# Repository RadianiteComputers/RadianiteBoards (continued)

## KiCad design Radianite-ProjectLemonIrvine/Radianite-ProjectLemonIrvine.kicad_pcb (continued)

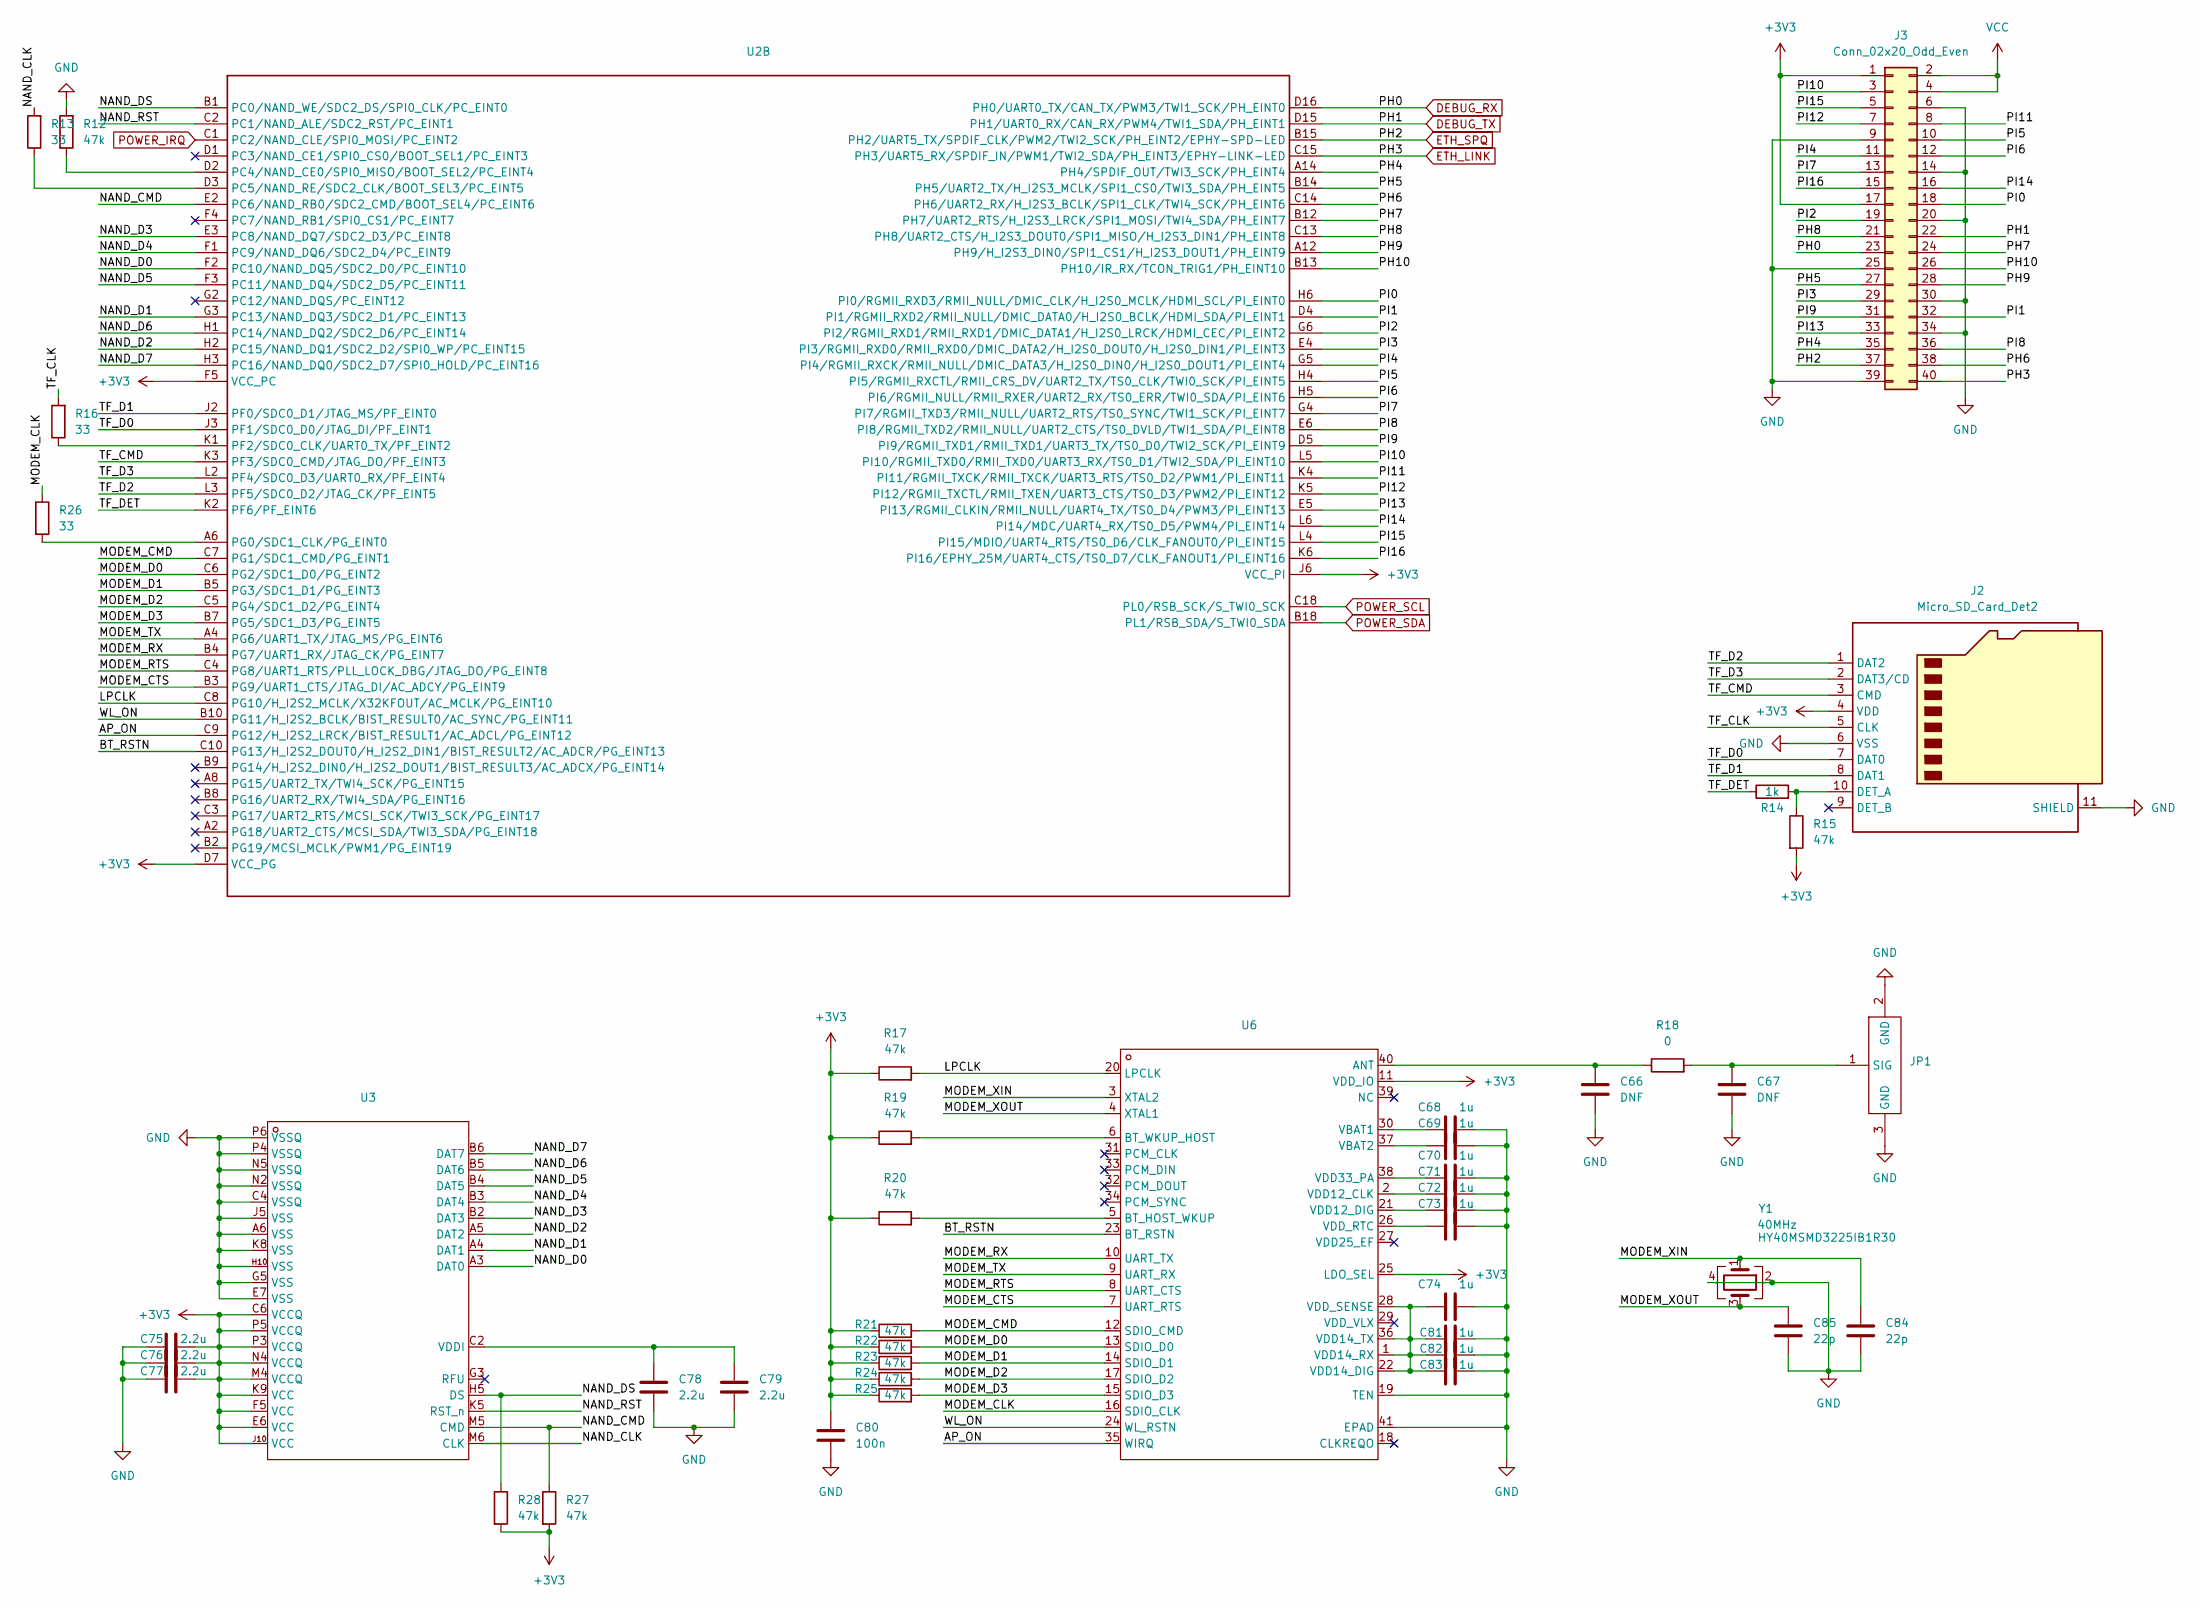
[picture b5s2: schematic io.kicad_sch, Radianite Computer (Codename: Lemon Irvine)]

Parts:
C66: DNF; C_0603_1608Metric
C67: DNF; C_0402_1005Metric
C68, C69, C70, C71, C72, C73, C74, C81, C82, C83: 1u; C_0402_1005Metric
C75, C76, C77, C78, C79: 2.2u; C_0402_1005Metric
C80: 100n; C_0402_1005Metric
C84, C85: 22p; C_0402_1005Metric
J2: Micro_SD_Card_Det2; microSD_HC_Molex_104031-0811
J3: Conn_02x20_Odd_Even; PinHeader_2x20_P2.54mm_Vertical
JP1: RF-SMD_734120114; Manufacturer Part U.FL-R-SMT-1(80); LCSC Part Name 3310472280，IPE-X板端 IPX接头，贴片
R12, R15, R17, R19, R20, R21, R22, R23, R24, R25, R27, R28: 47k; R_0402_1005Metric
R13, R16, R26: 33; R_0402_1005Metric
R14: 1k; R_0402_1005Metric
R18: 0; R_0402_1005Metric
U2: BGA284P65B1200_1400H125
U3: FBGA-153_L13.0-W11.5; Manufacturer Part EMMC04G-M627-A01
U6: QFN-40_L5.0-W5.0-P0.40-BL-EP3.4
Y1: 40MHz; Crystal_SMD_3225-4Pin_3.2x2.5mm

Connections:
+3V3: C75.2, C76.2, C77.2, C80.1, J2.4 (VDD), J3.1, J3.17, R15.2, R17.1, R19.1, R20.1, R21.1, R22.1, R23.1, R24.1, R25.1, R27.2, R28.2, U2.D7 (VCC_PG), U2.F5 (VCC_PC), U2.J6 (VCC_PI), U3.C6 (VCCQ), U3.E6 (VCC), U3.F5 (VCC), U3.J10 (VCC), U3.K9 (VCC), U3.M4 (VCCQ), U3.N4 (VCCQ), U3.P3 (VCCQ), U3.P5 (VCCQ), U6.11 (VDD_IO), U6.25 (LDO_SEL); also elsewhere on the board
/IO/AP_ON: U2.C9 (PG12/H_I2S2_LRCK/BIST_RESULT1/AC_ADCL/P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), U6.35 (WIRQ)
/IO/BT_RSTN: U2.C10 (PG13/H_I2S2_DOUT0/H_I2S2_DIN1/BIST_RESU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), U6.23 (BT_RSTN)
/IO/LPCLK: R17.2, U2.C8 (PG10/H_I2S2_MCLK/X32KFOUT/AC_MCLK/PG_EI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), U6.20 (LPCLK)
/IO/MODEM_CLK: R26.1, U6.16 (SDIO_CLK)
/IO/MODEM_CMD: R21.2, U2.C7 (PG1/SDC1_CMD/PG_EINT1), U6.12 (SDIO_CMD)
/IO/MODEM_CTS: U2.B3 (PG9/UART1_CTS/JTAG_DI/AC_ADCY/PG_EINT9), U6.7 (UART_RTS)
/IO/MODEM_D0: R22.2, U2.C6 (PG2/SDC1_D0/PG_EINT2), U6.13 (SDIO_D0)
/IO/MODEM_D1: R23.2, U2.B5 (PG3/SDC1_D1/PG_EINT3), U6.14 (SDIO_D1)
/IO/MODEM_D2: R24.2, U2.C5 (PG4/SDC1_D2/PG_EINT4), U6.17 (SDIO_D2)
/IO/MODEM_D3: R25.2, U2.B7 (PG5/SDC1_D3/PG_EINT5), U6.15 (SDIO_D3)
/IO/MODEM_RTS: U2.C4 (PG8/UART1_RTS/PLL_LOCK_DBG/JTAG_DO/PG_E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), U6.8 (UART_CTS)
/IO/MODEM_RX: U2.B4 (PG7/UART1_RX/JTAG_CK/PG_EINT7), U6.10 (UART_TX)
/IO/MODEM_TX: U2.A4 (PG6/UART1_TX/JTAG_MS/PG_EINT6), U6.9 (UART_RX)
/IO/MODEM_XIN: C84.1, U6.3 (XTAL2), Y1.1
/IO/MODEM_XOUT: C85.1, U6.4 (XTAL1), Y1.3
/IO/NAND_CLK: R13.2, U3.M6 (CLK)
/IO/NAND_CMD: R27.1, U2.E2 (PC6/NAND_RB0/SDC2_CMD/BOOT_SEL4/PC_EINT6), U3.M5 (CMD)
/IO/NAND_D0: U2.F2 (PC10/NAND_DQ5/SDC2_D0/PC_EINT10), U3.A3 (DAT0)
/IO/NAND_D1: U2.G3 (PC13/NAND_DQ3/SDC2_D1/PC_EINT13), U3.A4 (DAT1)
/IO/NAND_D2: U2.H2 (PC15/NAND_DQ1/SDC2_D2/SPI0_WP/PC_EINT15), U3.A5 (DAT2)
/IO/NAND_D3: U2.E3 (PC8/NAND_DQ7/SDC2_D3/PC_EINT8), U3.B2 (DAT3)
/IO/NAND_D4: U2.F1 (PC9/NAND_DQ6/SDC2_D4/PC_EINT9), U3.B3 (DAT4)
/IO/NAND_D5: U2.F3 (PC11/NAND_DQ4/SDC2_D5/PC_EINT11), U3.B4 (DAT5)
/IO/NAND_D6: U2.H1 (PC14/NAND_DQ2/SDC2_D6/PC_EINT14), U3.B5 (DAT6)
/IO/NAND_D7: U2.H3 (PC16/NAND_DQ0/SDC2_D7/SPI0_HOLD/PC_EINT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), U3.B6 (DAT7)
/IO/NAND_DS: R28.1, U2.B1 (PC0/NAND_WE/SDC2_DS/SPI0_CLK/PC_EINT0), U3.H5 (DS)
/IO/NAND_RST: U2.C2 (PC1/NAND_ALE/SDC2_RST/PC_EINT1), U3.K5 (RST_n)
/IO/PH4: J3.35, U2.A14 (PH4/SPDIF_OUT/TWI3_SCK/PH_EINT4)
/IO/PH5: J3.27, U2.B14 (PH5/UART2_TX/H_I2S3_MCLK/SPI1_CS0/TWI3_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)
/IO/PH6: J3.38, U2.C14 (PH6/UART2_RX/H_I2S3_BCLK/SPI1_CLK/TWI4_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)
/IO/PH7: J3.24, U2.B12 (PH7/UART2_RTS/H_I2S3_LRCK/SPI1_MOSI/TWI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)
/IO/PH8: J3.21, U2.C13 (PH8/UART2_CTS/H_I2S3_DOUT0/SPI1_MISO/H_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)
/IO/PH9: J3.28, U2.A12 (PH9/H_I2S3_DIN0/SPI1_CS1/H_I2S3_DOUT1/P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)
/IO/PH10: J3.26, U2.B13 (PH10/IR_RX/TCON_TRIG1/PH_EINT10)
/IO/PI0: J3.18, U2.H6 (PI0/RGMII_RXD3/RMII_NULL/DMIC_CLK/H_I2S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)
/IO/PI1: J3.32, U2.D4 (PI1/RGMII_RXD2/RMII_NULL/DMIC_DATA0/H_I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)
/IO/PI2: J3.19, U2.G6 (PI2/RGMII_RXD1/RMII_RXD1/DMIC_DATA1/H_I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)
/IO/PI3: J3.29, U2.E4 (PI3/RGMII_RXD0/RMII_RXD0/DMIC_DATA2/H_I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)
/IO/PI4: J3.11, U2.G5 (PI4/RGMII_RXCK/RMII_NULL/DMIC_DATA3/H_I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)
/IO/PI5: J3.10, U2.H4 (PI5/RGMII_RXCTL/RMII_CRS_DV/UART2_TX/TS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)
/IO/PI6: J3.12, U2.H5 (PI6/RGMII_NULL/RMII_RXER/UART2_RX/TS0_E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)
/IO/PI7: J3.13, U2.G4 (PI7/RGMII_TXD3/RMII_NULL/UART2_RTS/TS0_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)
/IO/PI8: J3.36, U2.E6 (PI8/RGMII_TXD2/RMII_NULL/UART2_CTS/TS0_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)
/IO/PI9: J3.31, U2.D5 (PI9/RGMII_TXD1/RMII_TXD1/UART3_TX/TS0_D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)
/IO/PI10: J3.3, U2.L5 (PI10/RGMII_TXD0/RMII_TXD0/UART3_RX/TS0_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)
/IO/PI11: J3.8, U2.K4 (PI11/RGMII_TXCK/RMII_TXCK/UART3_RTS/TS0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)
/IO/PI12: J3.7, U2.K5 (PI12/RGMII_TXCTL/RMII_TXEN/UART3_CTS/TS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)
/IO/PI13: J3.33, U2.E5 (PI13/RGMII_CLKIN/RMII_NULL/UART4_TX/TS0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)
/IO/PI14: J3.16, U2.L6 (PI14/MDC/UART4_RX/TS0_D5/PWM4/PI_EINT14)
/IO/PI15: J3.5, U2.L4 (PI15/MDIO/UART4_RTS/TS0_D6/CLK_FANOUT0/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)
/IO/PI16: J3.15, U2.K6 (PI16/EPHY_25M/UART4_CTS/TS0_D7/CLK_FANO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)
/IO/TF_CLK: J2.5 (CLK), R16.2
/IO/TF_CMD: J2.3 (CMD), U2.K3 (PF3/SDC0_CMD/JTAG_DO/PF_EINT3)
/IO/TF_D0: J2.7 (DAT0), U2.J3 (PF1/SDC0_D0/JTAG_DI/PF_EINT1)
/IO/TF_D1: J2.8 (DAT1), U2.J2 (PF0/SDC0_D1/JTAG_MS/PF_EINT0)
/IO/TF_D2: J2.1 (DAT2), U2.L3 (PF5/SDC0_D2/JTAG_CK/PF_EINT5)
/IO/TF_D3: J2.2 (DAT3/CD), U2.L2 (PF4/SDC0_D3/UART0_RX/PF_EINT4)
/IO/TF_DET: R14.1, U2.K2 (PF6/PF_EINT6)
/IO/WL_ON: U2.B10 (PG11/H_I2S2_BCLK/BIST_RESULT0/AC_SYNC/P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), U6.24 (WL_RSTN)
DEBUG_RX: J3.23, U2.D16 (PH0/UART0_TX/CAN_TX/PWM3/TWI1_SCK/PH_EI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); also elsewhere on the board
DEBUG_TX: J3.22, U2.D15 (PH1/UART0_RX/CAN_RX/PWM4/TWI1_SDA/PH_EI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); also elsewhere on the board
ETH_LINK: J3.40, U2.C15 (PH3/UART5_RX/SPDIF_IN/PWM1/TWI2_SDA/PH_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); also elsewhere on the board
ETH_SPQ: J3.37, U2.B15 (PH2/UART5_TX/SPDIF_CLK/PWM2/TWI2_SCK/PH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); also elsewhere on the board
GND: C66.2, C67.2, C68.2, C69.2, C70.2, C71.2, C72.2, C73.2, C74.2, C75.1, C76.1, C77.1, C78.2, C79.2, C80.2, C81.2, C82.2, C83.2, C84.2, C85.2, J2.6 (VSS), J2.11 (SHIELD), J3.6, J3.9, J3.14, J3.20, J3.25, J3.30, J3.34, J3.39, JP1.2 (GND), JP1.3 (GND), R12.2, U3.A6 (VSS), U3.C4 (VSSQ), U3.E7 (VSS), U3.G5 (VSS), U3.H10 (VSS), U3.J5 (VSS), U3.K8 (VSS), U3.N2 (VSSQ), U3.N5 (VSSQ), U3.P4 (VSSQ), U3.P6 (VSSQ), U6.19 (TEN), U6.41 (EPAD), Y1.2, Y1.4; also elsewhere on the board
unnamed: J2.10 (DET_A), R14.2, R15.1
unnamed: C67.1, JP1.1 (SIG), R18.2
unnamed: R12.1, U2.D2 (PC4/NAND_CE0/SPI0_MISO/BOOT_SEL2/PC_EIN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)
unnamed: R13.1, U2.D3 (PC5/NAND_RE/SDC2_CLK/BOOT_SEL3/PC_EINT5)
unnamed: R16.1, U2.K1 (PF2/SDC0_CLK/UART0_TX/PF_EINT2)
unnamed: R26.2, U2.A6 (PG0/SDC1_CLK/PG_EINT0)
unnamed: C78.1, C79.1, U3.C2 (VDDI)
unnamed: C66.1, R18.1, U6.40 (ANT)
unnamed: R20.2, U6.5 (BT_HOST_WKUP)
unnamed: R19.2, U6.6 (BT_WKUP_HOST)
unnamed: C68.1, U6.30 (VBAT1)
unnamed: C69.1, U6.37 (VBAT2)
unnamed: C71.1, U6.2 (VDD12_CLK)
unnamed: C72.1, U6.21 (VDD12_DIG)
unnamed: C74.1, C81.1, C82.1, C83.1, U6.1 (VDD14_RX), U6.22 (VDD14_DIG), U6.28 (VDD_SENSE), U6.36 (VDD14_TX)
unnamed: C70.1, U6.38 (VDD33_PA)
unnamed: C73.1, U6.26 (VDD_RTC)
POWER_IRQ: U2.C1 (PC2/NAND_CLE/SPI0_MOSI/PC_EINT2); also elsewhere on the board
POWER_SCL: U2.C18 (PL0/RSB_SCK/S_TWI0_SCK); also elsewhere on the board
POWER_SDA: U2.B18 (PL1/RSB_SDA/S_TWI0_SDA); also elsewhere on the board
VBUS: J3.2, J3.4; also elsewhere on the board

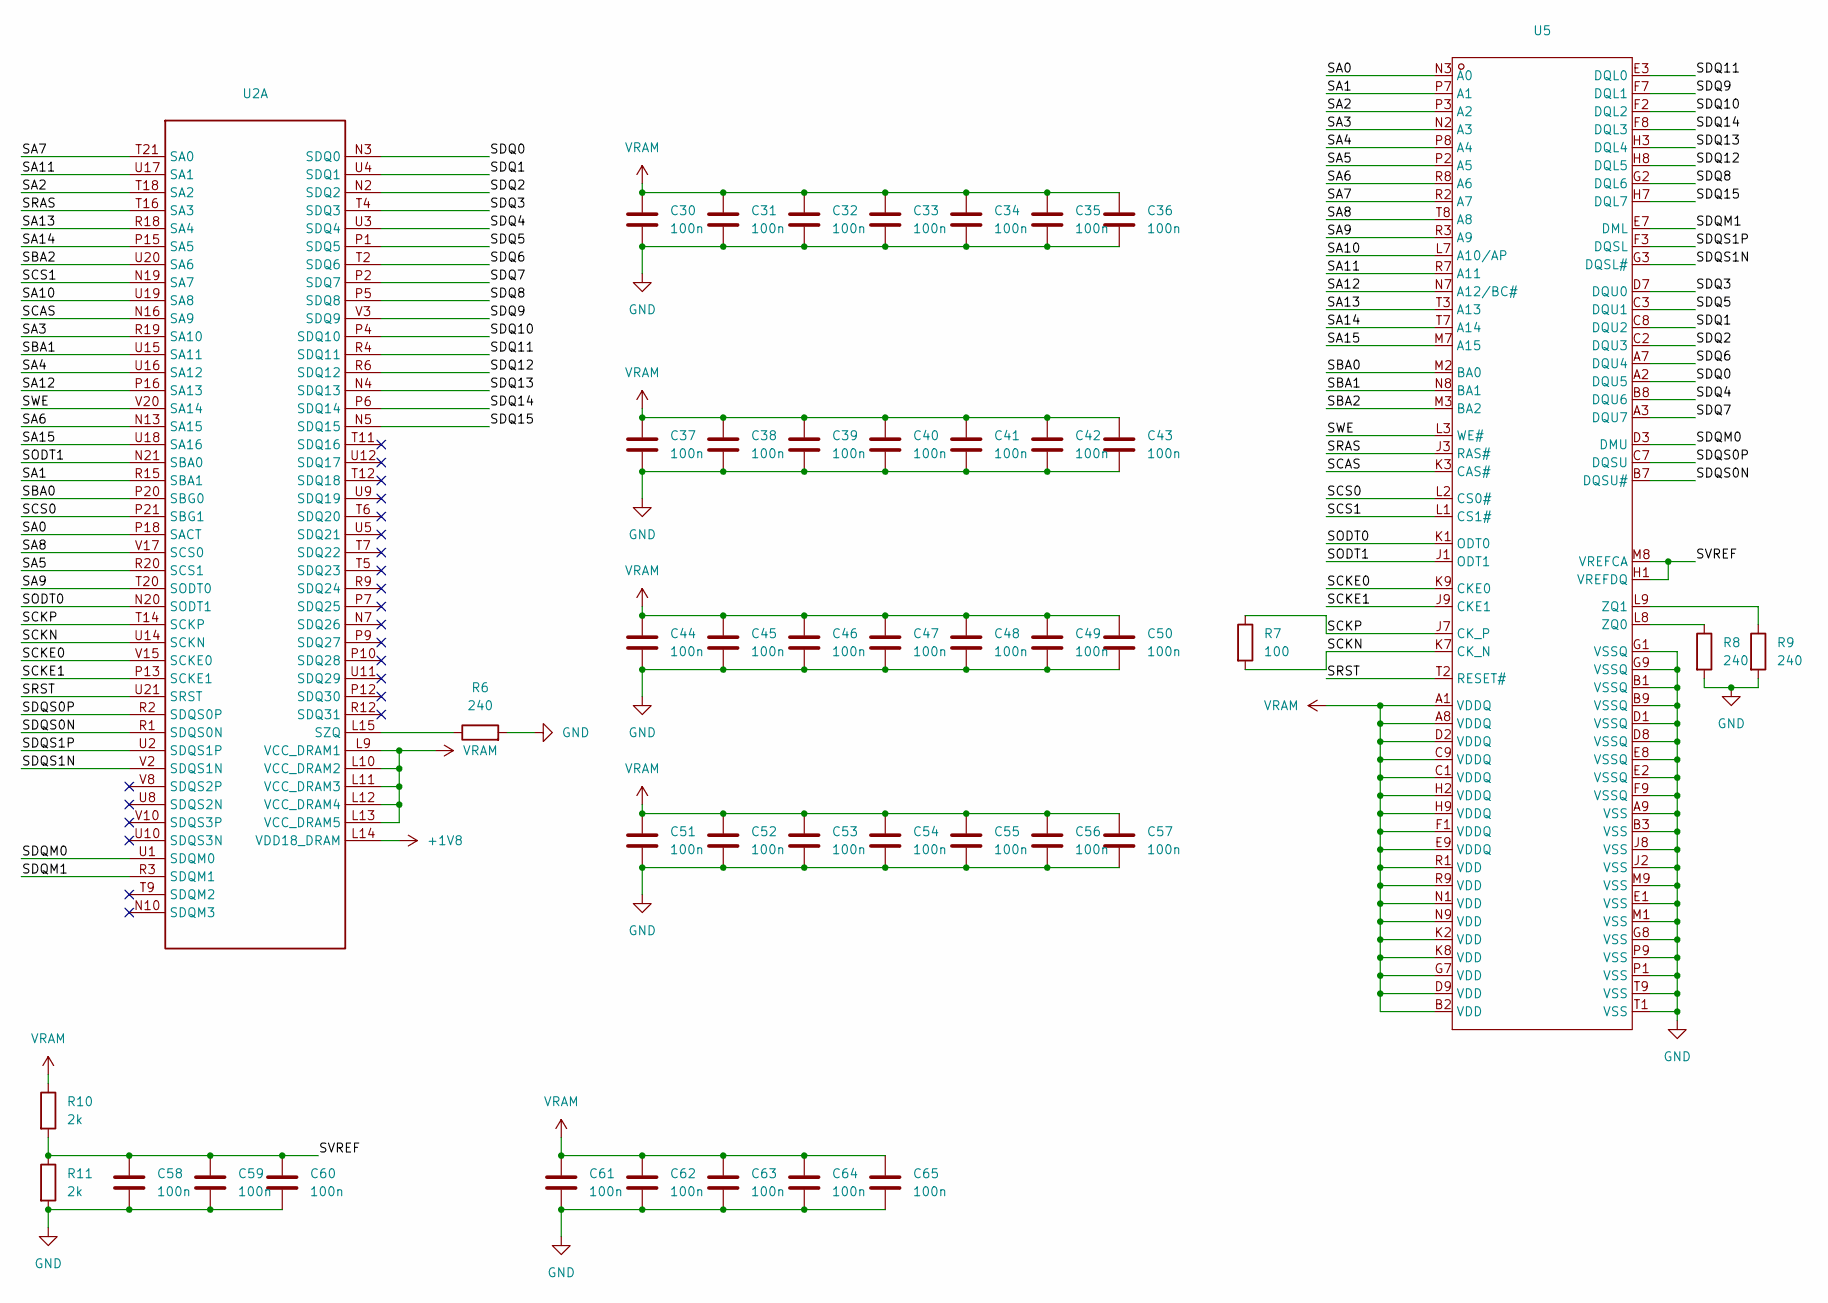
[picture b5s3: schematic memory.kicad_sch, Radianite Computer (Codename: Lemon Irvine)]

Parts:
C30, C31, C32, C33, C34, C35, C36, C37, C38, C39, C40, C41, C42, C43, C44, C45, C46, C47, C48, C49, C50, C51, C52, C53, C54, C55, C56, C57, C58, C59, C60, C61, C62, C63, C64, C65: 100n; C_0402_1005Metric
R6, R8, R9: 240; R_0402_1005Metric
R7: 100; R_0402_1005Metric
R10, R11: 2k; R_0402_1005Metric
U2: BGA284P65B1200_1400H125
U5: FBGA96; Manufacturer Part H5TQ4G63EFR-RDC

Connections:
+1V8: U2.L14 (VDD18_DRAM); also elsewhere on the board
/Memory/SA0: U2.P18 (SACT), U5.N3 (A0)
/Memory/SA1: U2.R15 (SBA1), U5.P7 (A1)
/Memory/SA2: U2.T18 (SA2), U5.P3 (A2)
/Memory/SA3: U2.R19 (SA10), U5.N2 (A3)
/Memory/SA4: U2.U16 (SA12), U5.P8 (A4)
/Memory/SA5: U2.R20 (SCS1), U5.P2 (A5)
/Memory/SA6: U2.N13 (SA15), U5.R8 (A6)
/Memory/SA7: U2.T21 (SA0), U5.R2 (A7)
/Memory/SA8: U2.V17 (SCS0), U5.T8 (A8)
/Memory/SA9: U2.T20 (SODT0), U5.R3 (A9)
/Memory/SA10: U2.U19 (SA8), U5.L7 (A10/AP)
/Memory/SA11: U2.U17 (SA1), U5.R7 (A11)
/Memory/SA12: U2.P16 (SA13), U5.N7 (A12/BC#)
/Memory/SA13: U2.R18 (SA4), U5.T3 (A13)
/Memory/SA14: U2.P15 (SA5), U5.T7 (A14)
/Memory/SA15: U2.U18 (SA16), U5.M7 (A15)
/Memory/SBA0: U2.P20 (SBG0), U5.M2 (BA0)
/Memory/SBA1: U2.U15 (SA11), U5.N8 (BA1)
/Memory/SBA2: U2.U20 (SA6), U5.M3 (BA2)
/Memory/SCAS: U2.N16 (SA9), U5.K3 (CAS#)
/Memory/SCKE0: U2.V15 (SCKE0), U5.K9 (CKE0)
/Memory/SCKE1: U2.P13 (SCKE1), U5.J9 (CKE1)
/Memory/SCKN: R7.2, U2.U14 (SCKN), U5.K7 (CK_N)
/Memory/SCKP: R7.1, U2.T14 (SCKP), U5.J7 (CK_P)
/Memory/SCS0: U2.P21 (SBG1), U5.L2 (CS0#)
/Memory/SCS1: U2.N19 (SA7), U5.L1 (CS1#)
/Memory/SDQ0: U2.N3 (SDQ0), U5.A2 (DQU5)
/Memory/SDQ1: U2.U4 (SDQ1), U5.C8 (DQU2)
/Memory/SDQ2: U2.N2 (SDQ2), U5.C2 (DQU3)
/Memory/SDQ3: U2.T4 (SDQ3), U5.D7 (DQU0)
/Memory/SDQ4: U2.U3 (SDQ4), U5.B8 (DQU6)
/Memory/SDQ5: U2.P1 (SDQ5), U5.C3 (DQU1)
/Memory/SDQ6: U2.T2 (SDQ6), U5.A7 (DQU4)
/Memory/SDQ7: U2.P2 (SDQ7), U5.A3 (DQU7)
/Memory/SDQ8: U2.P5 (SDQ8), U5.G2 (DQL6)
/Memory/SDQ9: U2.V3 (SDQ9), U5.F7 (DQL1)
/Memory/SDQ10: U2.P4 (SDQ10), U5.F2 (DQL2)
/Memory/SDQ11: U2.R4 (SDQ11), U5.E3 (DQL0)
/Memory/SDQ12: U2.R6 (SDQ12), U5.H8 (DQL5)
/Memory/SDQ13: U2.N4 (SDQ13), U5.H3 (DQL4)
/Memory/SDQ14: U2.P6 (SDQ14), U5.F8 (DQL3)
/Memory/SDQ15: U2.N5 (SDQ15), U5.H7 (DQL7)
/Memory/SDQM0: U2.U1 (SDQM0), U5.D3 (DMU)
/Memory/SDQM1: U2.R3 (SDQM1), U5.E7 (DML)
/Memory/SDQS0N: U2.R1 (SDQS0N), U5.B7 (DQSU#)
/Memory/SDQS0P: U2.R2 (SDQS0P), U5.C7 (DQSU)
/Memory/SDQS1N: U2.V2 (SDQS1N), U5.G3 (DQSL#)
/Memory/SDQS1P: U2.U2 (SDQS1P), U5.F3 (DQSL)
/Memory/SODT0: U2.N20 (SODT1), U5.K1 (ODT0)
/Memory/SODT1: U2.N21 (SBA0), U5.J1 (ODT1)
/Memory/SRAS: U2.T16 (SA3), U5.J3 (RAS#)
/Memory/SRST: U2.U21 (SRST), U5.T2 (RESET#)
/Memory/SVREF: C58.1, C59.1, C60.1, R10.2, R11.1, U5.H1 (VREFDQ), U5.M8 (VREFCA)
/Memory/SWE: U2.V20 (SA14), U5.L3 (WE#)
GND: C30.2, C31.2, C32.2, C33.2, C34.2, C35.2, C36.2, C37.2, C38.2, C39.2, C40.2, C41.2, C42.2, C43.2, C44.2, C45.2, C46.2, C47.2, C48.2, C49.2, C50.2, C51.2, C52.2, C53.2, C54.2, C55.2, C56.2, C57.2, C58.2, C59.2, C60.2, C61.2, C62.2, C63.2, C64.2, C65.2, R6.2, R8.2, R9.2, R11.2, U5.A9 (VSS), U5.B1 (VSSQ), U5.B3 (VSS), U5.B9 (VSSQ), U5.D1 (VSSQ), U5.D8 (VSSQ), U5.E1 (VSS), U5.E2 (VSSQ), U5.E8 (VSSQ), U5.F9 (VSSQ), U5.G1 (VSSQ), U5.G8 (VSS), U5.G9 (VSSQ), U5.J2 (VSS), U5.J8 (VSS), U5.M1 (VSS), U5.M9 (VSS), U5.P1 (VSS), U5.P9 (VSS), U5.T1 (VSS), U5.T9 (VSS); also elsewhere on the board
unnamed: R6.1, U2.L15 (SZQ)
unnamed: R8.1, U5.L8 (ZQ0)
unnamed: R9.1, U5.L9 (ZQ1)
VRAM: C30.1, C31.1, C32.1, C33.1, C34.1, C35.1, C36.1, C37.1, C38.1, C39.1, C40.1, C41.1, C42.1, C43.1, C44.1, C45.1, C46.1, C47.1, C48.1, C49.1, C50.1, C51.1, C52.1, C53.1, C54.1, C55.1, C56.1, C57.1, C61.1, C62.1, C63.1, C64.1, C65.1, R10.1, U2.L9 (VCC_DRAM1), U2.L10 (VCC_DRAM2), U2.L11 (VCC_DRAM3), U2.L12 (VCC_DRAM4), U2.L13 (VCC_DRAM5), U5.A1 (VDDQ), U5.A8 (VDDQ), U5.B2 (VDD), U5.C1 (VDDQ), U5.C9 (VDDQ), U5.D2 (VDDQ), U5.D9 (VDD), U5.E9 (VDDQ), U5.F1 (VDDQ), U5.G7 (VDD), U5.H2 (VDDQ), U5.H9 (VDDQ), U5.K2 (VDD), U5.K8 (VDD), U5.N1 (VDD), U5.N9 (VDD), U5.R1 (VDD), U5.R9 (VDD); also elsewhere on the board

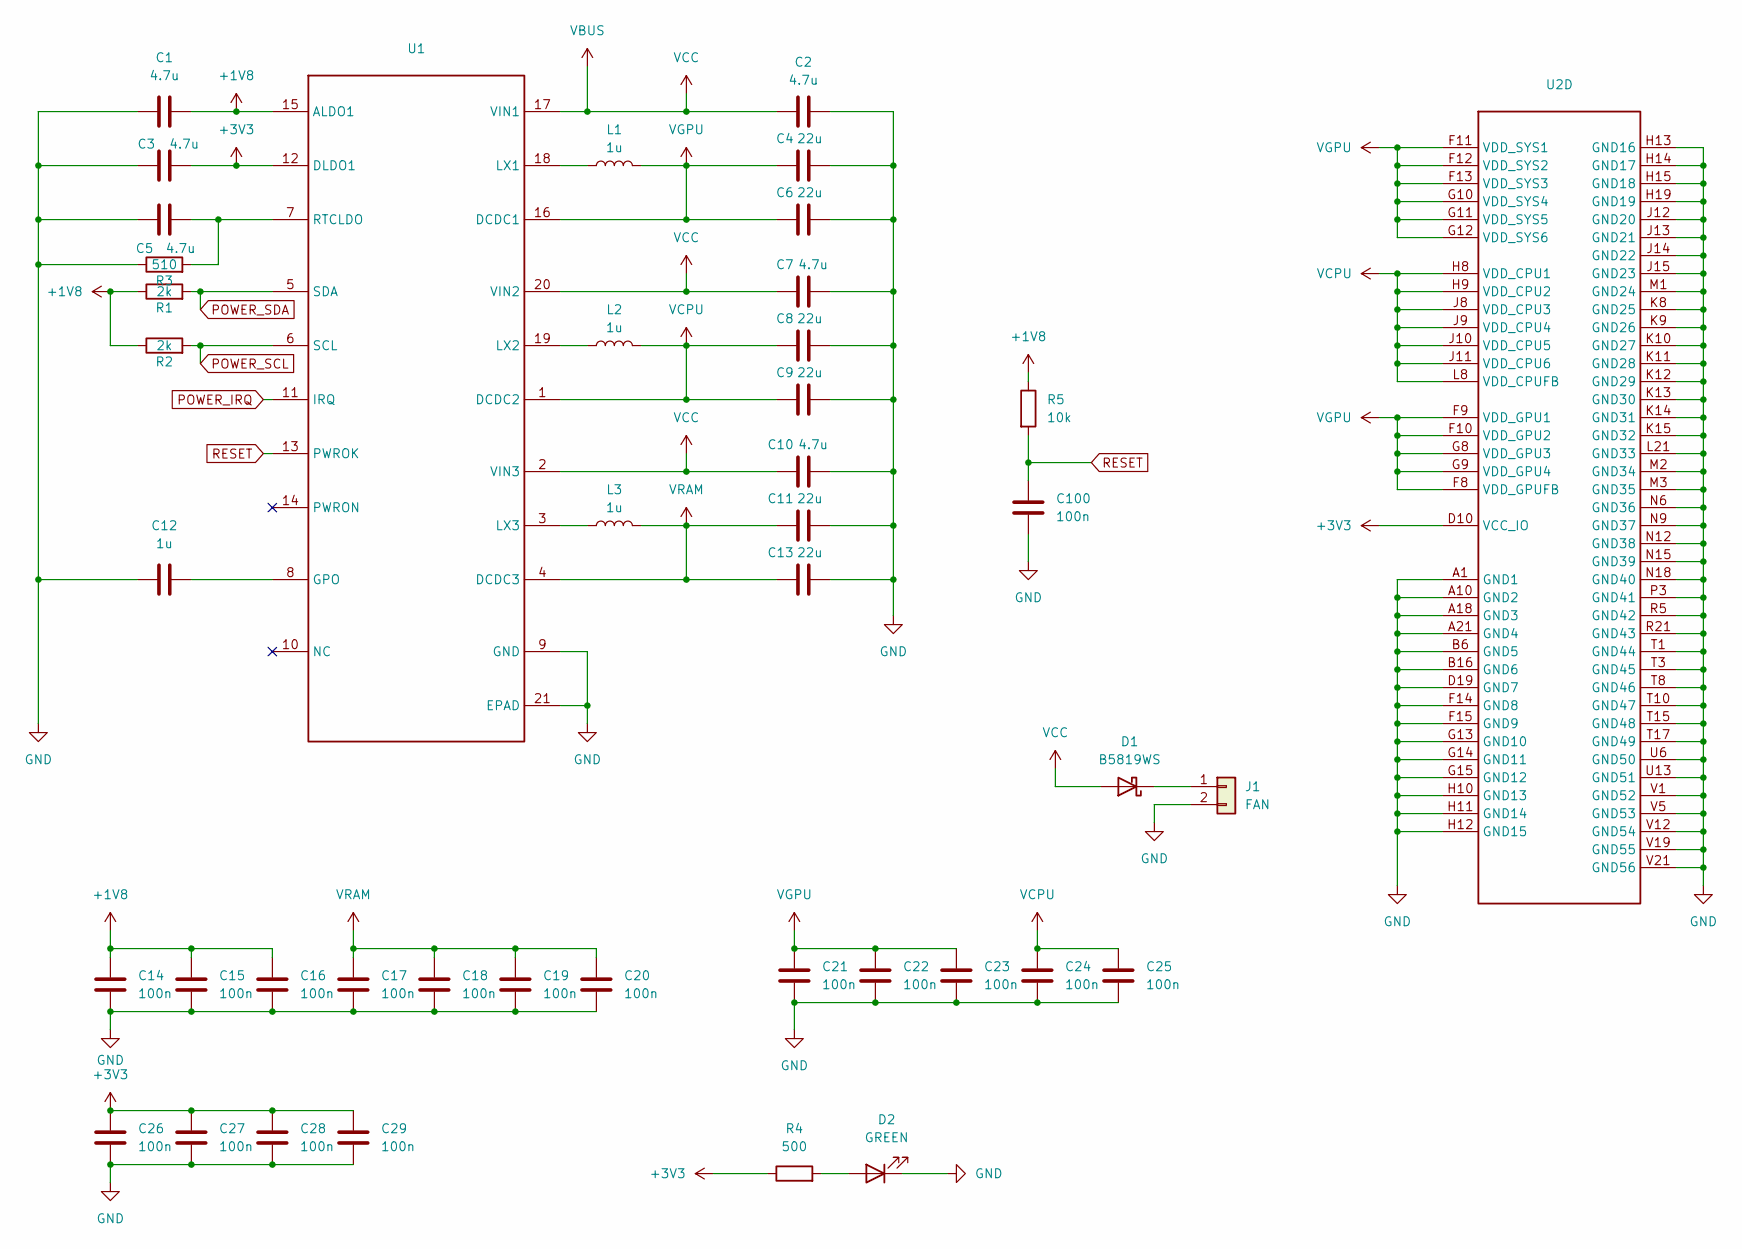
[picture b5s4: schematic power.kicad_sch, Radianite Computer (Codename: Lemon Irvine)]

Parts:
C1, C2, C3, C5, C7, C10: 4.7u; C_0402_1005Metric
C4, C6, C8, C9, C11, C13: 22u; C_0402_1005Metric
C12: 1u; C_0402_1005Metric
C14, C15, C16, C17, C18, C19, C20, C21, C22, C23, C24, C25, C26, C27, C28, C29, C100: 100n; C_0402_1005Metric
D1: B5819WS; D_SOD-323
D2: GREEN; LED_0402_1005Metric
J1: FAN; JST_PH_B2B-PH-K_1x02_P2.00mm_Vertical
L1, L2, L3: 1u; L_1008_2520Metric
R1, R2: 2k; R_0402_1005Metric
R3: 510; R_0402_1005Metric
R4: 500; R_0402_1005Metric
R5: 10k; R_0402_1005Metric
U1: WQFN-20_L3.0-W3.0-P0.40-BL-EP
U2: BGA284P65B1200_1400H125

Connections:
+1V8: C1.2, C14.1, C15.1, C16.1, R1.1, R2.1, R5.1, U1.15 (ALDO1); also elsewhere on the board
+3V3: C3.2, C26.1, C27.1, C28.1, C29.1, R4.1, U1.12 (DLDO1), U2.D10 (VCC_IO); also elsewhere on the board
GND: C1.1, C2.2, C3.1, C4.2, C5.1, C6.2, C7.2, C8.2, C9.2, C10.2, C11.2, C12.1, C13.2, C14.2, C15.2, C16.2, C17.2, C18.2, C19.2, C20.2, C21.2, C22.2, C23.2, C24.2, C25.2, C26.2, C27.2, C28.2, C29.2, C100.2, D2.1 (K), J1.2, R3.1, U1.9 (GND), U1.21 (EPAD), U2.A1 (GND1), U2.A10 (GND2), U2.A18 (GND3), U2.A21 (GND4), U2.B6 (GND5), U2.B16 (GND6), U2.D19 (GND7), U2.F14 (GND8), U2.F15 (GND9), U2.G13 (GND10), U2.G14 (GND11), U2.G15 (GND12), U2.H10 (GND13), U2.H11 (GND14), U2.H12 (GND15), U2.H13 (GND16), U2.H14 (GND17), U2.H15 (GND18), U2.H19 (GND19), U2.J12 (GND20), U2.J13 (GND21), U2.J14 (GND22), U2.J15 (GND23), U2.K8 (GND25), U2.K9 (GND26), U2.K10 (GND27), U2.K11 (GND28), U2.K12 (GND29), U2.K13 (GND30), U2.K14 (GND31), U2.K15 (GND32), U2.L21 (GND33), U2.M1 (GND24), U2.M2 (GND34), U2.M3 (GND35), U2.N6 (GND36), U2.N9 (GND37), U2.N12 (GND38), U2.N15 (GND39), U2.N18 (GND40), U2.P3 (GND41), U2.R5 (GND42), U2.R21 (GND43), U2.T1 (GND44), U2.T3 (GND45), U2.T8 (GND46), U2.T10 (GND47), U2.T15 (GND48), U2.T17 (GND49), U2.U6 (GND50), U2.U13 (GND51), U2.V1 (GND52), U2.V5 (GND53), U2.V12 (GND54), U2.V19 (GND55), U2.V21 (GND56); also elsewhere on the board
unnamed: D1.1 (K), J1.1
unnamed: D2.2 (A), R4.2
unnamed: C12.2, U1.8 (GPO)
unnamed: L1.1, U1.18 (LX1)
unnamed: L2.1, U1.19 (LX2)
unnamed: L3.1, U1.3 (LX3)
unnamed: C5.2, R3.2, U1.7 (RTCLDO)
POWER_IRQ: U1.11 (IRQ); also elsewhere on the board
POWER_SCL: R2.2, U1.6 (SCL); also elsewhere on the board
POWER_SDA: R1.2, U1.5 (SDA); also elsewhere on the board
RESET: C100.1, R5.2, U1.13 (PWROK); also elsewhere on the board
VBUS: C2.1, C7.1, C10.1, D1.2 (A), U1.2 (VIN3), U1.17 (VIN1), U1.20 (VIN2); also elsewhere on the board
VCPU: C8.1, C9.1, C24.1, C25.1, L2.2, U1.1 (DCDC2), U2.H8 (VDD_CPU1), U2.H9 (VDD_CPU2), U2.J8 (VDD_CPU3), U2.J9 (VDD_CPU4), U2.J10 (VDD_CPU5), U2.J11 (VDD_CPU6), U2.L8 (VDD_CPUFB)
VGPU: C4.1, C6.1, C21.1, C22.1, C23.1, L1.2, U1.16 (DCDC1), U2.F8 (VDD_GPUFB), U2.F9 (VDD_GPU1), U2.F10 (VDD_GPU2), U2.F11 (VDD_SYS1), U2.F12 (VDD_SYS2), U2.F13 (VDD_SYS3), U2.G8 (VDD_GPU3), U2.G9 (VDD_GPU4), U2.G10 (VDD_SYS4), U2.G11 (VDD_SYS5), U2.G12 (VDD_SYS6)
VRAM: C11.1, C13.1, C17.1, C18.1, C19.1, C20.1, L3.2, U1.4 (DCDC3); also elsewhere on the board

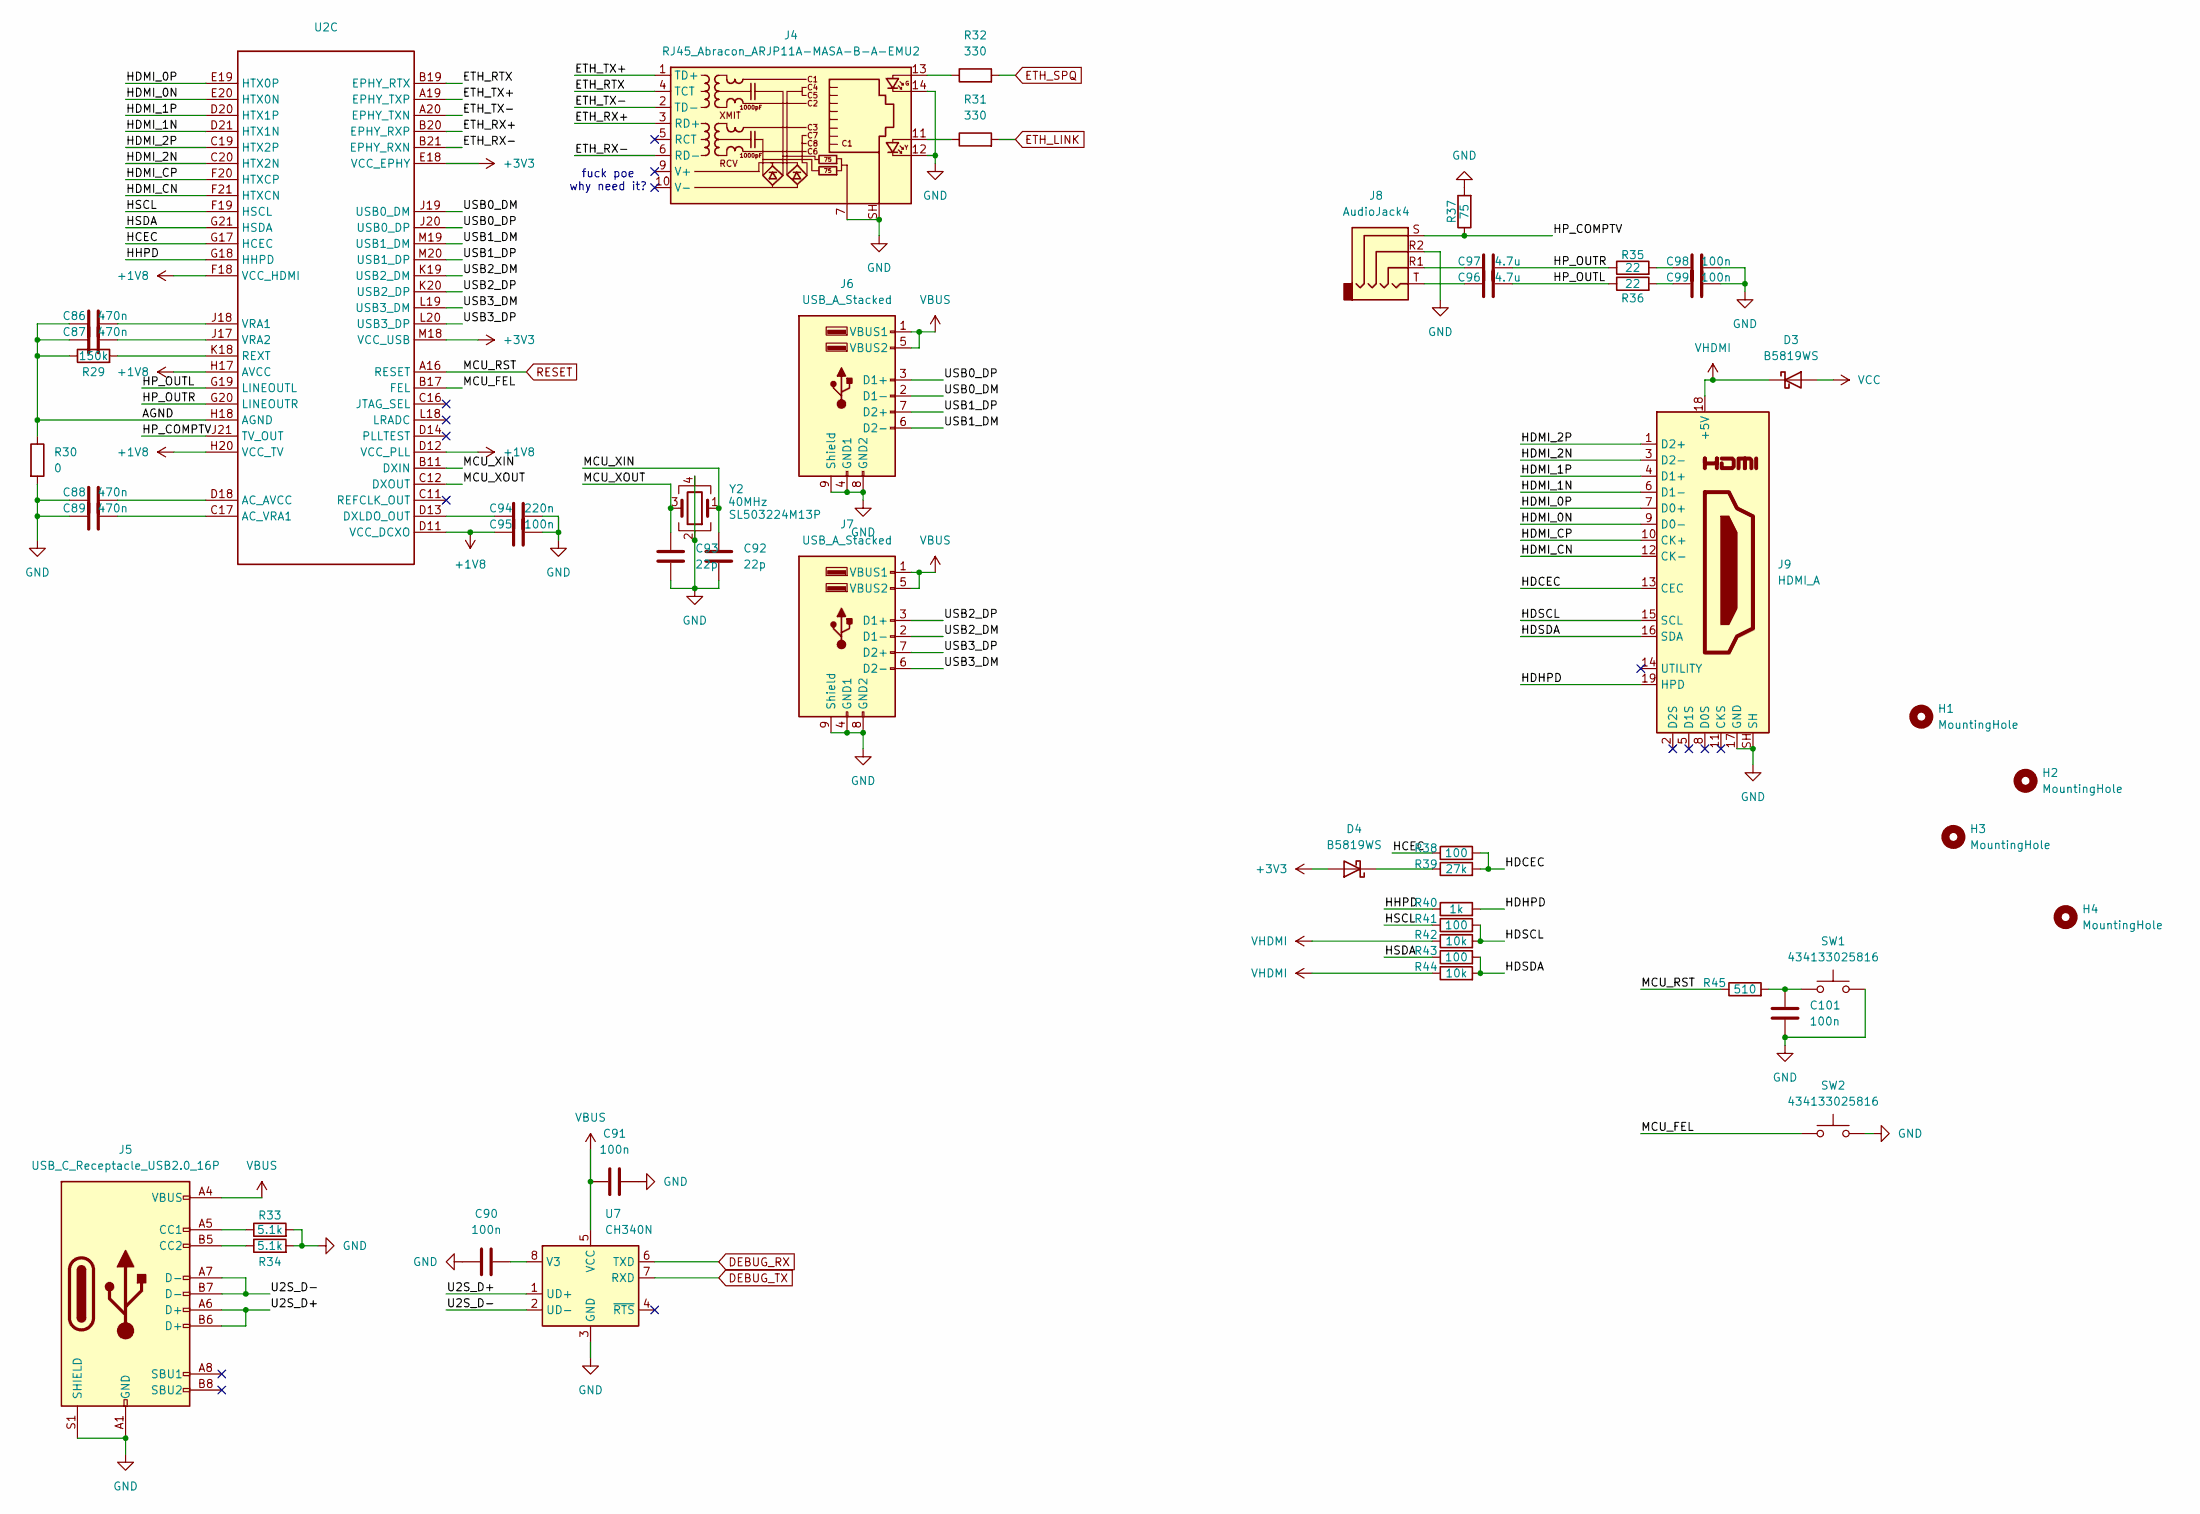
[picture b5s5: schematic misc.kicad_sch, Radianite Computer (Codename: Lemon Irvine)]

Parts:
C86, C87, C88, C89: 470n; C_0402_1005Metric
C90, C91, C95, C98, C99, C101: 100n; C_0402_1005Metric
C92, C93: 22p; C_0402_1005Metric
C94: 220n; C_0402_1005Metric
C96, C97: 4.7u; C_0402_1005Metric
D3, D4: B5819WS; D_SOD-323
H1, H2, H3, H4: MountingHole; MountingHole_2.7mm_M2.5_ISO14580
J4: RJ45_Abracon_ARJP11A-MASA-B-A-EMU2; RJ45_Abracon_ARJP11A-MA_Horizontal
J5: USB_C_Receptacle_USB2.0_16P; USB_C_Receptacle_GCT_USB4105-xx-A_16P_TopMnt_Horizontal
J6, J7: USB_A_Stacked; USB_A_Wuerth_61400826021_Horizontal_Stacked
J8: AudioJack4; Jack_3.5mm_PJ320E_Horizontal
J9: HDMI_A; HDMI_A_Molex_208658-1001_Horizontal
R29: 150k; R_0402_1005Metric
R30: 0; R_0402_1005Metric
R31, R32: 330; R_0402_1005Metric
R33, R34: 5.1k; R_0402_1005Metric
R35, R36: 22; R_0402_1005Metric
R37: 75; R_0402_1005Metric
R38, R41, R43: 100; R_0402_1005Metric
R39: 27k; R_0402_1005Metric
R40: 1k; R_0402_1005Metric
R42, R44: 10k; R_0402_1005Metric
R45: 510; R_0402_1005Metric
SW1, SW2: 434133025816; SW_Push_1P1T_NO_Vertical_Wuerth_434133025816
U2: BGA284P65B1200_1400H125
U7: CH340N; SOP-8_3.9x4.9mm_P1.27mm
Y2: 40MHz; Crystal_SMD_3225-4Pin_3.2x2.5mm

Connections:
+1V8: C95.1, U2.D11 (VCC_DCXO), U2.D12 (VCC_PLL), U2.F18 (VCC_HDMI), U2.H17 (AVCC), U2.H20 (VCC_TV); also elsewhere on the board
+3V3: D4.2 (A), U2.E18 (VCC_EPHY), U2.M18 (VCC_USB); also elsewhere on the board
/Miscellaneous/AGND: C86.1, C87.1, R29.1, R30.1, U2.H18 (AGND)
/Miscellaneous/ETH_RTX: J4.4 (TCT), U2.B19 (EPHY_RTX)
/Miscellaneous/ETH_RX+: J4.3 (RD+), U2.B20 (EPHY_RXP)
/Miscellaneous/ETH_RX-: J4.6 (RD-), U2.B21 (EPHY_RXN)
/Miscellaneous/ETH_TX+: J4.1 (TD+), U2.A19 (EPHY_TXP)
/Miscellaneous/ETH_TX-: J4.2 (TD-), U2.A20 (EPHY_TXN)
/Miscellaneous/HCEC: R38.1, U2.G17 (HCEC)
/Miscellaneous/HDCEC: J9.13 (CEC), R38.2, R39.2
/Miscellaneous/HDHPD: J9.19 (HPD), R40.2
/Miscellaneous/HDMI_0N: J9.9 (D0-), U2.E20 (HTX0N)
/Miscellaneous/HDMI_0P: J9.7 (D0+), U2.E19 (HTX0P)
/Miscellaneous/HDMI_1N: J9.6 (D1-), U2.D21 (HTX1N)
/Miscellaneous/HDMI_1P: J9.4 (D1+), U2.D20 (HTX1P)
/Miscellaneous/HDMI_2N: J9.3 (D2-), U2.C20 (HTX2N)
/Miscellaneous/HDMI_2P: J9.1 (D2+), U2.C19 (HTX2P)
/Miscellaneous/HDMI_CN: J9.12 (CK-), U2.F21 (HTXCN)
/Miscellaneous/HDMI_CP: J9.10 (CK+), U2.F20 (HTXCP)
/Miscellaneous/HDSCL: J9.15 (SCL), R41.2, R42.2
/Miscellaneous/HDSDA: J9.16 (SDA), R43.2, R44.2
/Miscellaneous/HHPD: R40.1, U2.G18 (HHPD)
/Miscellaneous/HP_COMPTV: J8.S, R37.1, U2.J21 (TV_OUT)
/Miscellaneous/HP_OUTL: C96.2, R36.1, U2.G19 (LINEOUTL)
/Miscellaneous/HP_OUTR: C97.2, R35.1, U2.G20 (LINEOUTR)
/Miscellaneous/HSCL: R41.1, U2.F19 (HSCL)
/Miscellaneous/HSDA: R43.1, U2.G21 (HSDA)
/Miscellaneous/MCU_FEL: SW2.1, U2.B17 (FEL)
/Miscellaneous/MCU_XIN: C92.1, U2.B11 (DXIN), Y2.1
/Miscellaneous/MCU_XOUT: C93.1, U2.C12 (DXOUT), Y2.3
/Miscellaneous/U2S_D+: J5.A6 (D+), J5.B6 (D+), U7.1 (UD+)
/Miscellaneous/U2S_D-: J5.A7 (D-), J5.B7 (D-), U7.2 (UD-)
/Miscellaneous/USB0_DM: J6.2 (D1-), U2.J19 (USB0_DM)
/Miscellaneous/USB0_DP: J6.3 (D1+), U2.J20 (USB0_DP)
/Miscellaneous/USB1_DM: J6.6 (D2-), U2.M19 (USB1_DM)
/Miscellaneous/USB1_DP: J6.7 (D2+), U2.M20 (USB1_DP)
/Miscellaneous/USB2_DM: J7.2 (D1-), U2.K19 (USB2_DM)
/Miscellaneous/USB2_DP: J7.3 (D1+), U2.K20 (USB2_DP)
/Miscellaneous/USB3_DM: J7.6 (D2-), U2.L19 (USB3_DM)
/Miscellaneous/USB3_DP: J7.7 (D2+), U2.L20 (USB3_DP)
DEBUG_RX: U7.6 (TXD); also elsewhere on the board
DEBUG_TX: U7.7 (RXD); also elsewhere on the board
ETH_LINK: R31.2; also elsewhere on the board
ETH_SPQ: R32.2; also elsewhere on the board
GND: C88.1, C89.1, C90.1, C91.1, C92.2, C93.2, C94.2, C95.2, C98.2, C99.2, C101.2, J4.7, J4.12, J4.14, J4.SH, J5.A1 (GND), J5.A12 (GND), J5.B1 (GND), J5.B12 (GND), J5.S1 (SHIELD), J6.4 (GND1), J6.8 (GND2), J6.9 (Shield), J7.4 (GND1), J7.8 (GND2), J7.9 (Shield), J8.R2, J9.17 (GND), J9.SH, R30.2, R33.2, R34.2, R37.2, SW1.2, SW2.2, U7.3 (GND), Y2.2, Y2.4; also elsewhere on the board
unnamed: C96.1, J8.T
unnamed: C97.1, J8.R1
unnamed: C98.1, R35.2
unnamed: C99.1, R36.2
unnamed: C101.1, R45.2, SW1.1
unnamed: D4.1 (K), R39.1
unnamed: J4.11, R31.1
unnamed: J4.13, R32.1
unnamed: J5.A5 (CC1), R33.1
unnamed: J5.B5 (CC2), R34.1
unnamed: C88.2, U2.D18 (AC_AVCC)
unnamed: C89.2, U2.C17 (AC_VRA1)
unnamed: C94.1, U2.D13 (DXLDO_OUT)
unnamed: R29.2, U2.K18 (REXT)
unnamed: C86.2, U2.J18 (VRA1)
unnamed: C87.2, U2.J17 (VRA2)
unnamed: C90.2, U7.8 (V3)
RESET: R45.1, U2.A16 (RESET); also elsewhere on the board
VBUS: C91.2, D3.2 (A), J5.A4 (VBUS), J5.A9 (VBUS), J5.B4 (VBUS), J5.B9 (VBUS), J6.1 (VBUS1), J6.5 (VBUS2), J7.1 (VBUS1), J7.5 (VBUS2), U7.5 (VCC); also elsewhere on the board
VHDMI: D3.1 (K), J9.18 (+5V), R42.1, R44.1

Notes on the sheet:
fuck poe why need it?
